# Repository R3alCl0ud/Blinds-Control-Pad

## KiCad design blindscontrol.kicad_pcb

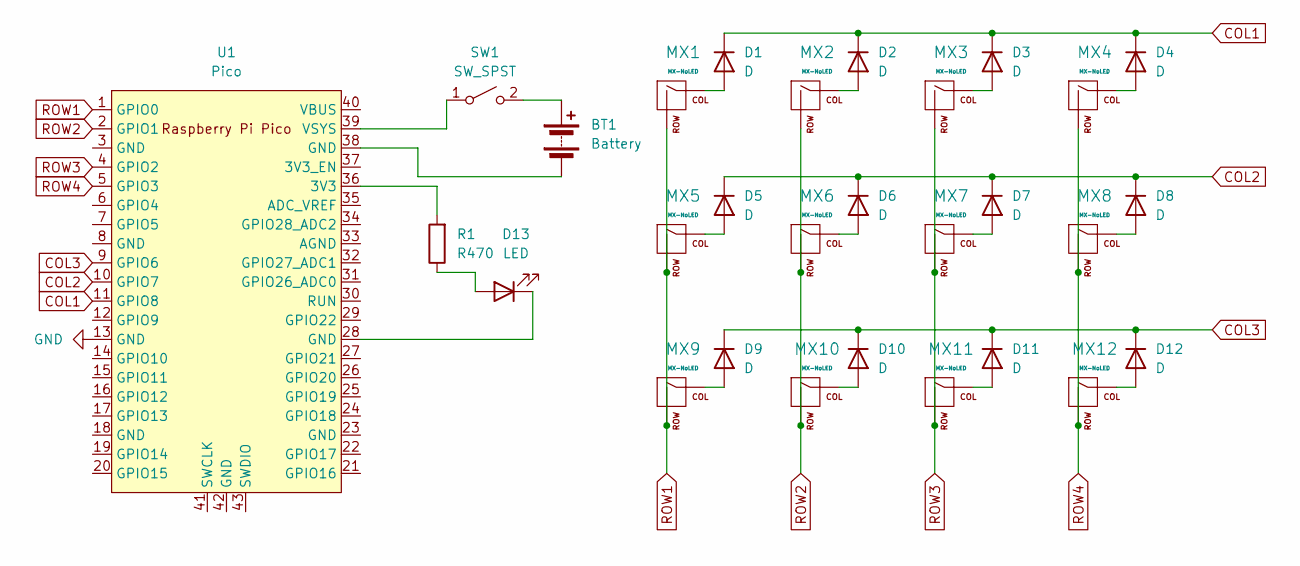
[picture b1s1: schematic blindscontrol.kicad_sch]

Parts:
BT1: Battery; BatteryHolder_MPD_BC2AAPC_2xAA
D1, D2, D3, D4, D5, D6, D7, D8, D9, D10, D11, D12: D; D_T-1_P5.08mm_Horizontal
D13: LED; D_T-1_P5.08mm_Horizontal
MX1, MX2, MX3, MX4, MX5, MX6, MX7, MX8, MX9, MX10, MX11, MX12: MX-NoLED; SW_Cherry_MX_1.00u_PCB
R1: R470; R_Axial_DIN0309_L9.0mm_D3.2mm_P12.70mm_Horizontal
SW1: SW_SPST; D_T-1_P5.08mm_Horizontal
U1: Pico; RPi_Pico_SMD_TH

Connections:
COL1: D1.1 (K), D2.1 (K), D3.1 (K), D4.1 (K), U1.11 (GPIO8)
COL2: D5.1 (K), D6.1 (K), D7.1 (K), D8.1 (K), U1.10 (GPIO7)
COL3: D9.1 (K), D10.1 (K), D11.1 (K), D12.1 (K), U1.9 (GPIO6)
GND: U1.13 (GND)
unnamed: BT1.1 (+), SW1.2 (B)
unnamed: BT1.2 (-), U1.38 (GND)
unnamed: D1.2 (A), MX1.1 (COL)
unnamed: D2.2 (A), MX2.1 (COL)
unnamed: D3.2 (A), MX3.1 (COL)
unnamed: D4.2 (A), MX4.1 (COL)
unnamed: D5.2 (A), MX5.1 (COL)
unnamed: D6.2 (A), MX6.1 (COL)
unnamed: D7.2 (A), MX7.1 (COL)
unnamed: D8.2 (A), MX8.1 (COL)
unnamed: D9.2 (A), MX9.1 (COL)
unnamed: D10.2 (A), MX10.1 (COL)
unnamed: D11.2 (A), MX11.1 (COL)
unnamed: D12.2 (A), MX12.1 (COL)
unnamed: D13.2 (A), R1.1
unnamed: D13.1 (K), U1.28 (GND)
unnamed: SW1.1 (A), U1.39 (VSYS)
unnamed: R1.2, U1.36 (3V3)
ROW1: MX1.2 (ROW), MX5.2 (ROW), MX9.2 (ROW), U1.1 (GPIO0)
ROW2: MX2.2 (ROW), MX6.2 (ROW), MX10.2 (ROW), U1.2 (GPIO1)
ROW3: MX3.2 (ROW), MX7.2 (ROW), MX11.2 (ROW), U1.4 (GPIO2)
ROW4: MX4.2 (ROW), MX8.2 (ROW), MX12.2 (ROW), U1.5 (GPIO3)

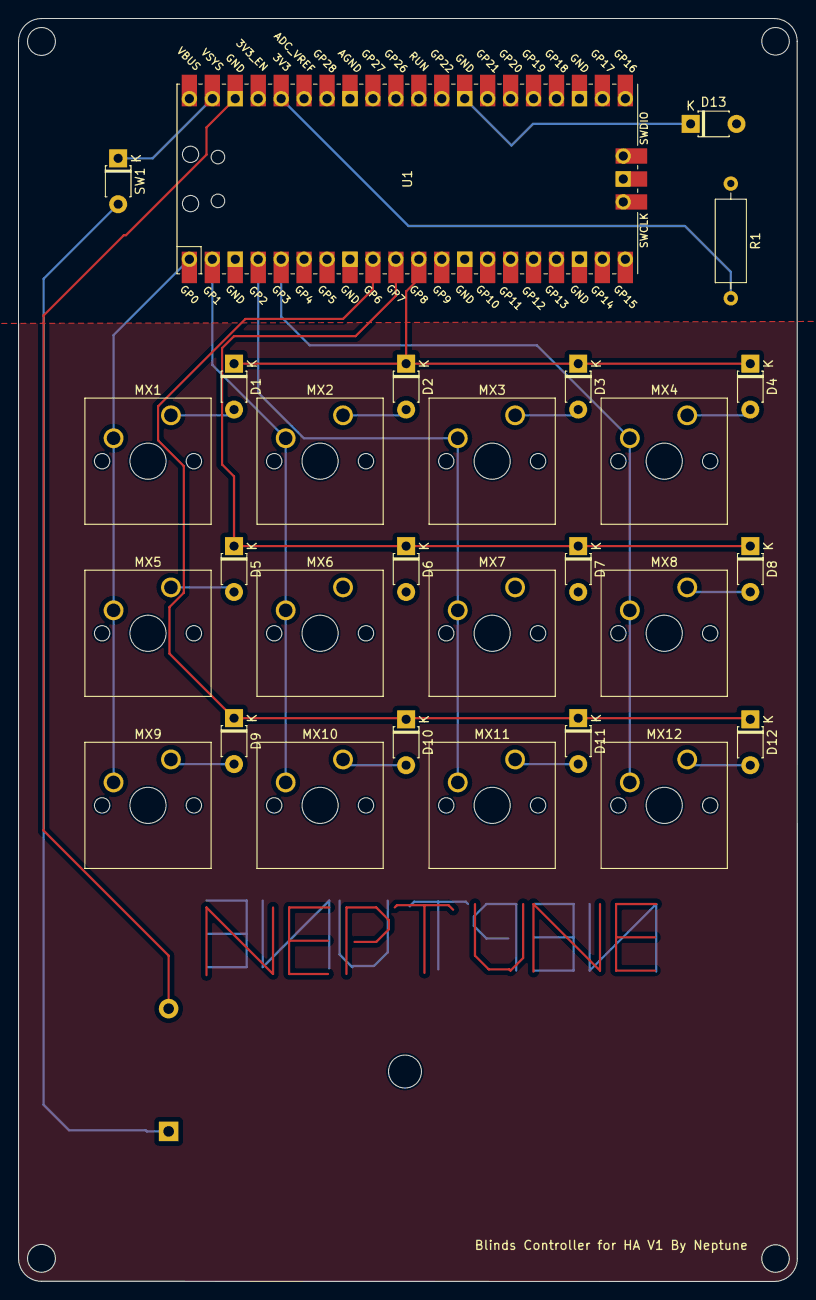
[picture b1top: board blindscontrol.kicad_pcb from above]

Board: 2 copper layers, 86.2 x 139.8 mm, 29 parts (1 on the bottom side), 25 nets.

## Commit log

2023-11-20 add stuff
2023-11-21 made some changes
    Also trying to export it for fusion360 so I can make a case around it
2023-11-22 more stuffs for case
